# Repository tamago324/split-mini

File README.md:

# split mini

小さな分割キーボードです。

## ライセンス

<br />この 作品 は <a rel="license" href="http://creativecommons.org/licenses/by/4.0/">クリエイティブ・コモンズ 表示 4.0 国際 ライセンス</a>の下に提供されています。

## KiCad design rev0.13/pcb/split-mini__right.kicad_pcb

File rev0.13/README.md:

## split mini rev0.13

* [KLE](http://www.keyboard-layout-editor.com/#/gists/a34cca681a2130594f6d9f4207fc3f27)
* https://kbplate.ai03.com/ でプレートデータを作成
  * width: 17
  * height: 17
* 左右分割キーボード
* 狭ピッチ
  * キーキャップは専用のものを使う (底面が16mmのやつを使うことにする)
  * [雰囲気で作ったキーキャップ](https://github.com/tamago324/small-keycaps)
* MXのみ 対応
* 100mmx100mm以下のため、Elecrow で1ドルで発注可能
* [QMK firmware](https://github.com/tamago324/qmk_firmware/tree/tamago324/keyboards/tamago324/splitmini)
  * rev13 のディレクトリのため、`nix-shell --run 'sudo make tamago324/splitmini/rev13:tamago324:flash'` のようにして書き込み可能

## 部品一覧

片手分

| 名前                      | 値    | 備考                | 個数 | 部品番号   | リンク        |
| ---                       | ---   | ---                 | ---  | ---        | ---           |
| コンデンサ                | 0.1uF | 0805 (2012)         | 3    | C2、C3、C4 | [Digikey][1]  |
| コンデンサ                | 10uF  | 0805 (2012)         | 1    | C5         | [Digikey][2]  |
| コンデンサ                | 1uF   | 0805 (2012)         | 1    | C1         | [Digikey][3]  |
| コンデンサ                | 22pF  | 0805 (2012)         | 2    | C6、C7     | [Digikey][4]  |
| ヒューズ                  | 500mA | 1206 (3216)         | 1    | F1         | [Digikey][5]  |
| 抵抗                      | 5.1kΩ  | 0805 (2012)         | 2    | R1、R2     | [モノタロウ][13]  |
| 抵抗                      | 22    | 0805 (2012)         | 2    | R3、R4     | [Digikey][7]  |
| 抵抗                      | 10kΩ  | 0805 (2012)         | 2    | R5、R6     | [Digikey][6]  |
| 水晶発振子                | 16MHz | 3225 4pin 3.2x2.5mm | 1    | Y1         | [Digikey][8]  |
| TRRSジャック (MJ-4PP-9)   | -     | -                   | 1    | J2         | [遊舎工房][9] |
| ATmega32U4                | -     | 10x10mm P0.8mm      | 1    | U1         | [Digikey][10] |
| USBコネクタ (Type-C) | -     | 5077CR-16SMC2-BK-TR    | 1    | J1       | [秋月電子][11] |
| リセットスイッチ          | -     | SKRPACE010            | 1    | RESET1        | [秋月電子][12] |

### 実際に購入したところ

| 名前                      | 値    | 備考                | 個数 | 部品番号   | リンク        |
| ---                       | ---   | ---                 | ---  | ---        | ---           |
| コンデンサ                | 0.1uF | 0805 (2012)         | 3    | C2、C3、C4 | [秋月電子][21]  |
| コンデンサ                | 10uF  | 0805 (2012)         | 1    | C5         | [秋月電子][22]  |
| コンデンサ                | 1uF   | 0805 (2012)         | 1    | C1         | [秋月電子][23]  |
| コンデンサ                | 22pF  | 0805 (2012)         | 2    | C6、C7     | [mouser][24]  |
| ヒューズ                  | 500mA | 1206 (3216)         | 1    | F1         | [mouser][25]  |
| 抵抗                      | 5.1kΩ  | 0805 (2012)         | 2    | R1、R2     | [モノタロウ][13]  |
| 抵抗                      | 22    | 0805 (2012)         | 2    | R3、R4     | [mouser][27]  |
| 抵抗                      | 10kΩ  | 0805 (2012)         | 2    | R5、R6     | [秋月電子][26]  |
| 水晶発振子                | 16MHz | 3225 4pin 3.2x2.5mm | 1    | Y1         | [秋月電子][28]  |
| TRRSジャック (MJ-4PP-9)   | -     | -                   | 1    | J1         | [遊舎工房][29] |
| ATmega32U4                | -     | 10x10mm P0.8mm      | 1    | U1         | [秋月電子][30] |
| USBコネクタ (Type-C) | -     | 5077CR-16SMC2-BK-TR    | 1    | J1       | [秋月電子][11] |
| リセットスイッチ          | -     | SKRPACE010           | 1    | SW1        | [秋月電子][12] |

### 画像

#### PCB

#### ケース

## 参考情報

* https://github.com/ruiqimao/keyboard-pcb-guide
* [ATmega32u2直付けのキーパッドを作ろう！](https://taro-hayashi.github.io/LetsMakeaKeypadWithAtmega32u2/)
* [ATMega32u4を使う場合の設計メモ\.md](https://gist.github.com/s-show/286ffb1f5d9c886b514ff7a37e6d8d37)
* [ATmega32U4について学んだこと](https://zenn.dev/koron/articles/a2e220d73800ba)
* [Using USB Type\-C on hobyist projects – The blog of Tyler Ward \(aka scorpia\)](https://www.scorpia.co.uk/2016/03/17/using-usb-type-c-on-hobyist-projects/)

[1]:https://www.digikey.com/product-detail/en/samsung-electro-mechanics/CL21B104MBCNNNC/1276-2450-1-ND/3890536
[2]:https://www.digikey.com/product-detail/en/samsung-electro-mechanics/CL21A106KOQNNNG/1276-6455-1-ND/5958083
[3]:https://www.digikey.com/product-detail/en/samsung-electro-mechanics/CL21B105KAFNNNE/1276-1066-1-ND/3889152
[4]:https://www.digikey.com/product-detail/en/samsung-electro-mechanics/CL21C220JB61PNC/1276-2605-1-ND/3890691
[5]:https://www.digikey.com/product-detail/en/bel-fuse-inc/0ZCJ0050AF2E/507-1803-1-ND/4156312
[6]:https://www.digikey.com/product-detail/en/panasonic-electronic-components/ERA-6AEB103V/P10KDACT-ND/1465971
[7]:https://www.digikey.com/product-detail/en/panasonic-electronic-components/ERJ-6GEYJ220V/P22ACT-ND/87316
[8]:https://www.digikey.com/product-detail/en/CX3225SB16000D0GZJC1/1253-1698-1-ND/5995245/?itemSeq=264931473
[9]:https://shop.yushakobo.jp/products/a0800tr-01-1
[10]:https://www.digikey.com/product-detail/en/microchip-technology/ATMEGA32U4-AU/ATMEGA32U4-AU-ND/1914602
[11]:https://akizukidenshi.com/catalog/g/gC-14356/
[12]:https://akizukidenshi.com/catalog/g/gP-06185/
[13]:https://www.monotaro.com/g/04269677/?t.q=5.1K%20%E3%83%81%E3%83%83%E3%83%97%E6%8A%B5%E6%8A%97

[21]:https://akizukidenshi.com/catalog/g/gP-00093/
[22]:https://akizukidenshi.com/catalog/g/gP-13606/
[23]:https://akizukidenshi.com/catalog/g/gP-15331/
[24]:https://www.mouser.jp/ProductDetail/Samsung-Electro-Mechanics/CL21C220JB61PNC?qs=uvHW8qpSFORHMf5PV5yOeg%3D%3D
[25]:https://www.mouser.jp/ProductDetail/Bel-Fuse/0ZCJ0050AF2E?qs=SRYZG9HaIQ3Oqm1PQp276Q%3D%3D
[26]:https://akizukidenshi.com/catalog/g/gR-11797/
[27]:https://www.mouser.jp/ProductDetail/Panasonic/ERJ-6GEYJ220V?qs=tQNqqtTOejK5J3XsPrLscg%3D%3D
[28]:https://akizukidenshi.com/catalog/g/gP-02457/
[29]:https://shop.yushakobo.jp/products/a0800tr-01-1
[30]:https://akizukidenshi.com/catalog/g/gI-09835/

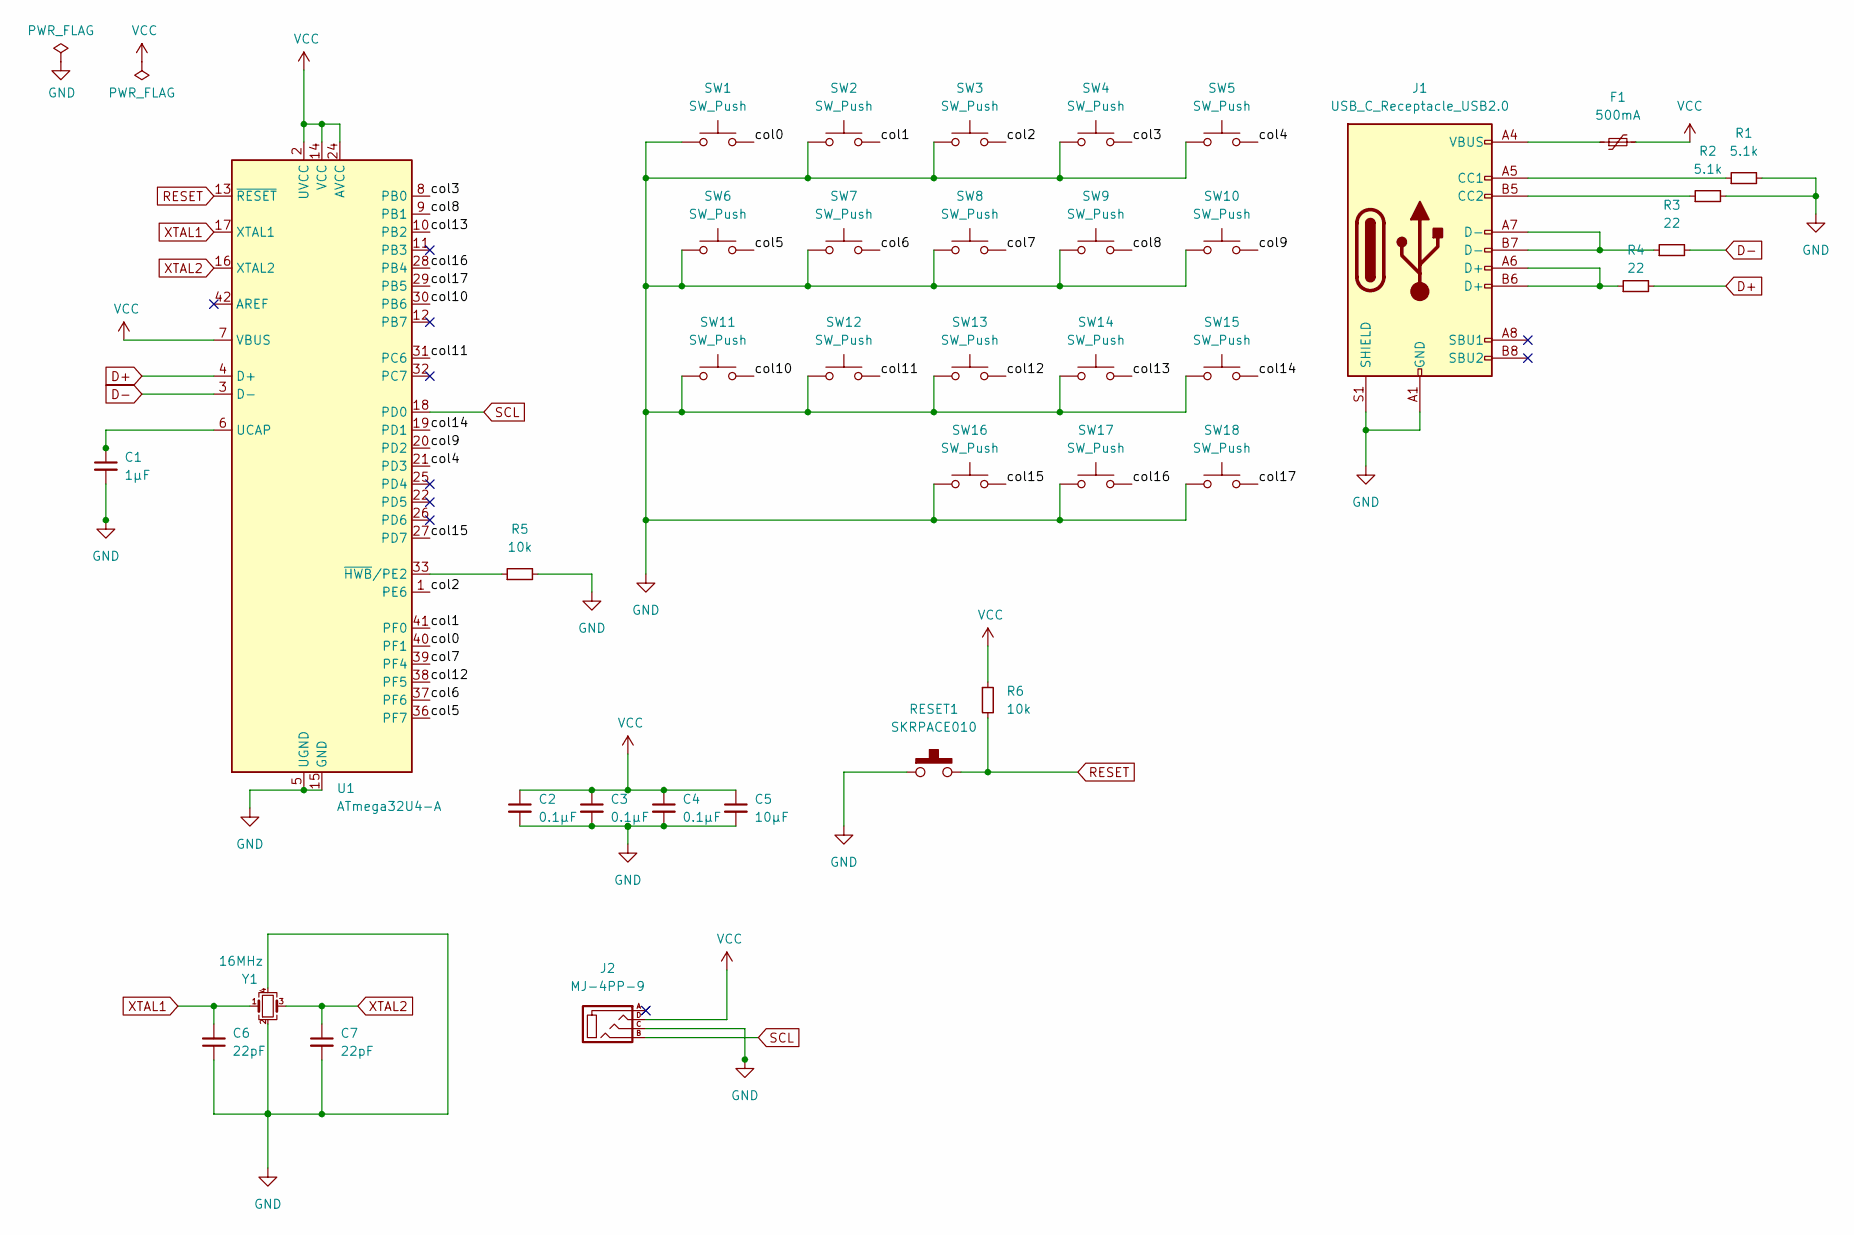
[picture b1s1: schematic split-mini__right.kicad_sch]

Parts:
C1: 1μF; C_0805_2012Metric; LCSC C28323
C2, C3, C4: 0.1μF; C_0805_2012Metric; LCSC C49678
C5: 10μF; C_0805_2012Metric; LCSC C440198
C6, C7: 22pF; C_0805_2012Metric; LCSC C1804
F1: 500mA; Fuse_1206_3216Metric; LCSC C883125
J1: USB_C_Receptacle_USB2.0; USB_C_Receptacle_Neltron_5077CR-16SMC2
J2: MJ-4PP-9; MJ-4PP-9_1side
R1, R2: 5.1k; R_0805_2012Metric; LCSC C17561
R3, R4: 22; R_0805_2012Metric; LCSC C17561
R5, R6: 10k; R_0805_2012Metric; LCSC C17414
RESET1: SKRPACE010; SKRPAxE010
SW1, SW2, SW3, SW4, SW5, SW6, SW7, SW8, SW9, SW10, SW11, SW12, SW13, SW14, SW15, SW16, SW17, SW18: SW_Push; CherryMX_Hotswap
U1: ATmega32U4-A; LQFP-44_10x10mm_P0.8mm
Y1: 16MHz; Crystal_SMD_SeikoEpson_FA238-4Pin_3.2x2.5mm_HandSoldering; LCSC C13738

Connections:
/col0: SW1.2, U1.40 (PF1)
/col1: SW2.2, U1.41 (PF0)
/col2: SW3.2, U1.1 (PE6)
/col3: SW4.2, U1.8 (PB0)
/col4: SW5.2, U1.21 (PD3)
/col5: SW6.2, U1.36 (PF7)
/col6: SW7.2, U1.37 (PF6)
/col7: SW8.2, U1.39 (PF4)
/col8: SW9.2, U1.9 (PB1)
/col9: SW10.2, U1.20 (PD2)
/col10: SW11.2, U1.30 (PB6)
/col11: SW12.2, U1.31 (PC6)
/col12: SW13.2, U1.38 (PF5)
/col13: SW14.2, U1.10 (PB2)
/col14: SW15.2, U1.19 (PD1)
/col15: SW16.2, U1.27 (PD7)
/col16: SW17.2, U1.28 (PB4)
/col17: SW18.2, U1.29 (PB5)
D+: R4.2, U1.4 (D+)
D-: R3.2, U1.3 (D-)
GND: C1.2, C2.2, C3.2, C4.2, C5.2, C6.1, C7.2, J1.A1 (GND), J1.A12 (GND), J1.B1 (GND), J1.B12 (GND), J1.S1 (SHIELD), J2.C, R1.2, R2.2, R5.2, RESET1.1 (A), RESET1.2 (B), SW1.1, SW2.1, SW3.1, SW4.1, SW5.1, SW6.1, SW7.1, SW8.1, SW9.1, SW10.1, SW11.1, SW12.1, SW13.1, SW14.1, SW15.1, SW16.1, SW17.1, SW18.1, U1.5 (UGND), U1.15 (GND), U1.23 (GND), U1.35 (GND), U1.43 (GND), Y1.2, Y1.4
unnamed: C1.1, U1.6 (UCAP)
unnamed: F1.1, J1.A4 (VBUS), J1.A9 (VBUS), J1.B4 (VBUS), J1.B9 (VBUS)
unnamed: J1.A5 (CC1), R1.1
unnamed: J1.A6 (D+), J1.B6 (D+), R4.1
unnamed: J1.A7 (D-), J1.B7 (D-), R3.1
unnamed: J1.B5 (CC2), R2.1
unnamed: R5.1, U1.33 (~HWB/PE2)
RESET: R6.2, RESET1.3 (C), RESET1.4 (D), U1.13 (~RESET)
SCL: J2.B, U1.18 (PD0)
VCC: C2.1, C3.1, C4.1, C5.1, F1.2, J2.D, R6.1, U1.2 (UVCC), U1.7 (VBUS), U1.14 (VCC), U1.24 (AVCC), U1.34 (VCC), U1.44 (AVCC)
XTAL1: C6.2, U1.17 (XTAL1), Y1.1
XTAL2: C7.1, U1.16 (XTAL2), Y1.3

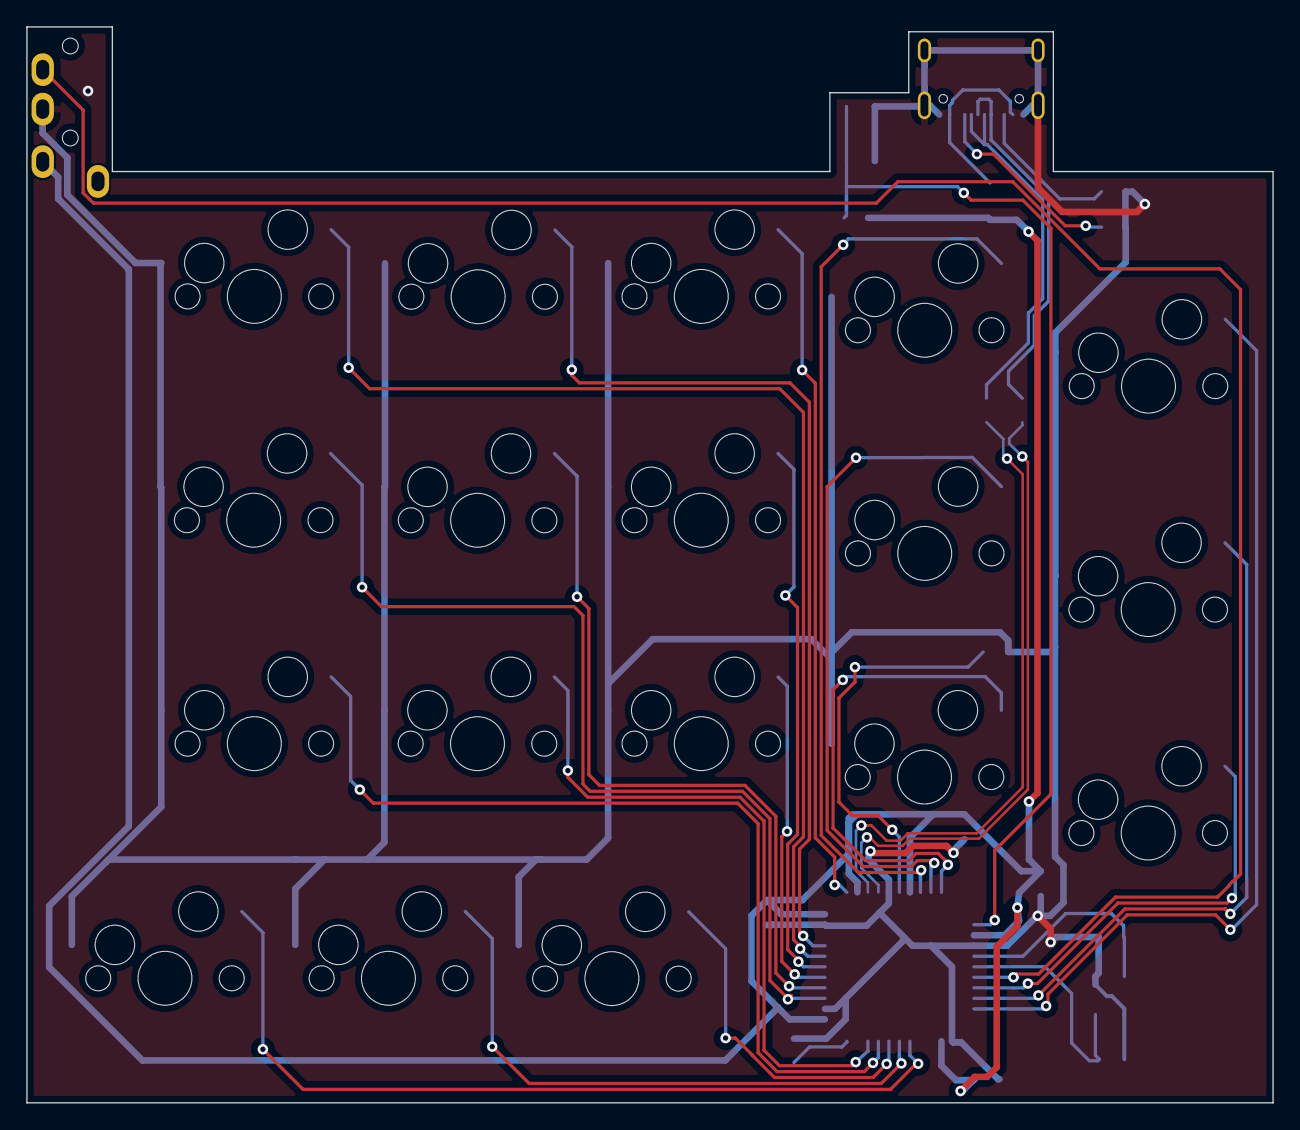
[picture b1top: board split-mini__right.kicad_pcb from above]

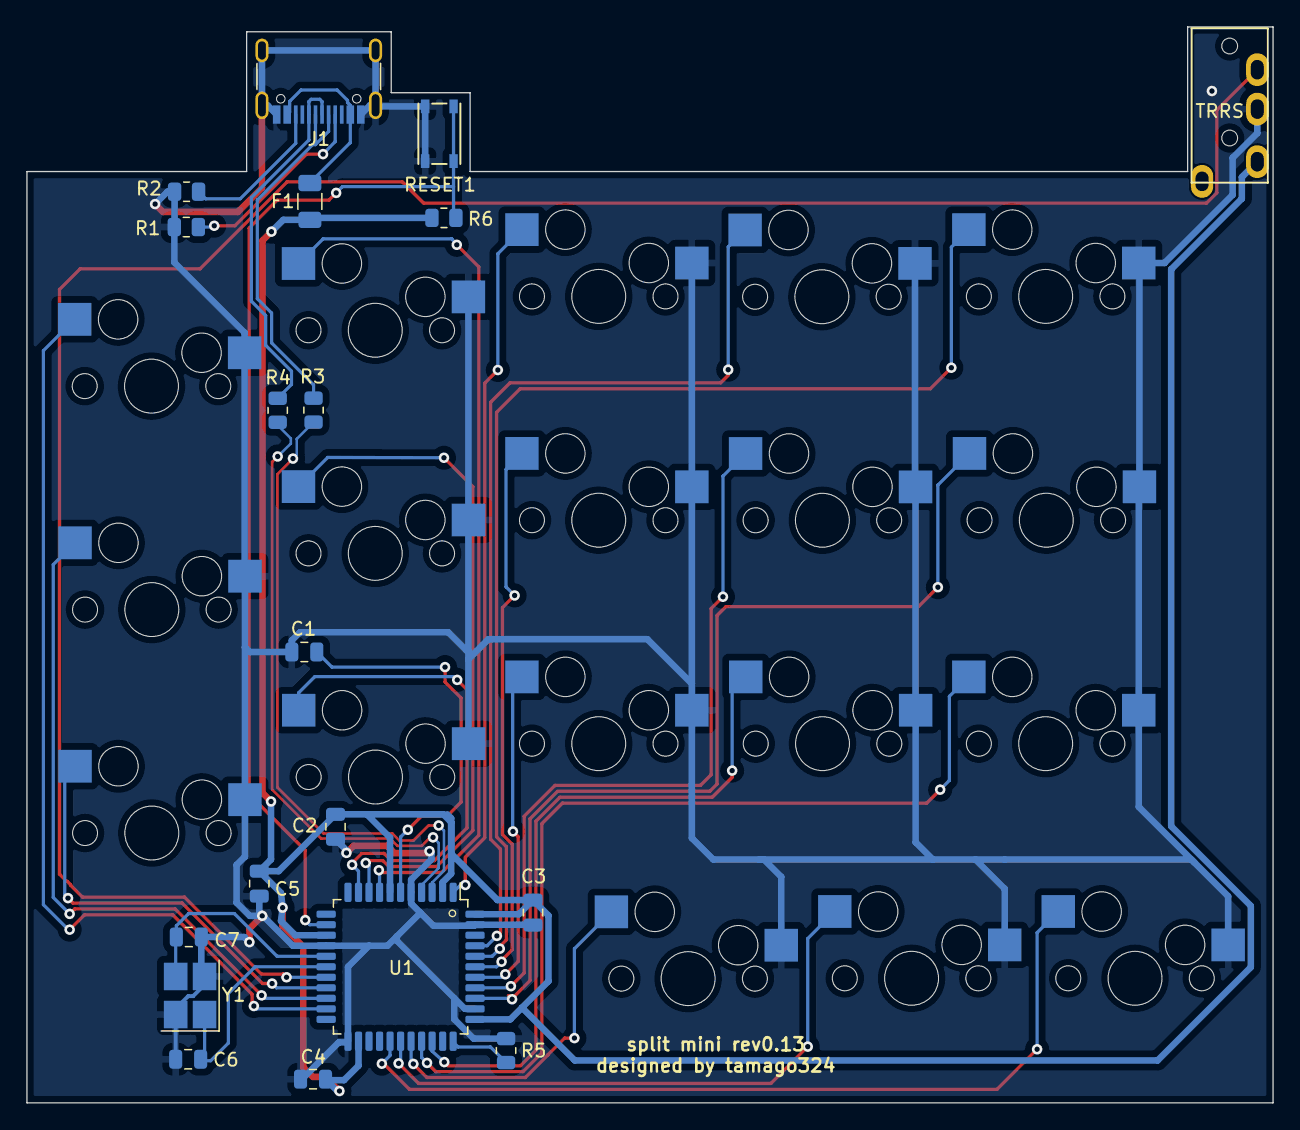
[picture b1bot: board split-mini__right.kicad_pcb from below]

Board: 2 copper layers, 94.8 x 81.8 mm, 37 parts (19 on the bottom side), 33 nets.

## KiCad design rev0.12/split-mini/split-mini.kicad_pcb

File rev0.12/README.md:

## split mini rev0.12

* ProMicro を使用
* [KLE](http://www.keyboard-layout-editor.com/##@_name=split%20mini%20rev0.13&notes=oyayubi%20ga%201.25%20ninatteiruyatu%0Amata,%20tatewo%2017.5%20ni%20sitai%3B&@_y:0.75&x:3&a:7%3B&=&=%3B&@_y:-0.9&x:5%3B&=%3B&@_y:-0.9500000000000001&x:2%3B&=%3B&@_y:-0.7&x:1%3B&=%3B&@_y:-0.44999999999999996&x:3%3B&=&=%3B&@_y:-0.8999999999999999&x:5%3B&=%3B&@_y:-0.9500000000000002&x:2%3B&=%3B&@_y:-0.6999999999999997&x:1%3B&=%3B&@_y:-0.4500000000000002&x:3%3B&=&=%3B&@_y:-0.8999999999999999&x:5%3B&=%3B&@_y:-0.9500000000000002&x:2%3B&=%3B&@_y:-0.6999999999999997&x:1%3B&=%3B&@_y:-0.3500000000000001&x:3.3%3B&=&_w:1.25%3B&=%3B&@_r:10&y:-2.05&x:6.3&w:1.25%3B&=)
* https://kbplate.ai03.com/ でプレートデータを作成
  * width: 16.5
  * height: 17.5
* 左右分割キーボード
* 狭ピッチ
  * キーキャップは専用のものを使う (底面が16mmのやつを使うことにする)
* MX 対応
* 100mmx100mm以下のため、Elecrow で1ドルで発注可能
  * PCB、トッププレート1つ、ボトムプレートの3つを3ドルで発注できて、2セット組み立てられる
* Trackball module をつけられる
  * 線をはんだ付けすることで使用可能になる想定
  * Aliexpress で売っているもの
    * [ケーブル](https://ja.aliexpress.com/item/4000898605030.html?spm=a2g0o.order_list.order_list_main.5.2968585aQbozum&gatewayAdapt=glo2jpn)
    * [コネクタ](https://ja.aliexpress.com/item/4001115739803.html?spm=a2g0o.order_list.order_list_main.11.2968585aQbozum&gatewayAdapt=glo2jpn)

## Pictures

### PCB

### Top plate

### bottom plate

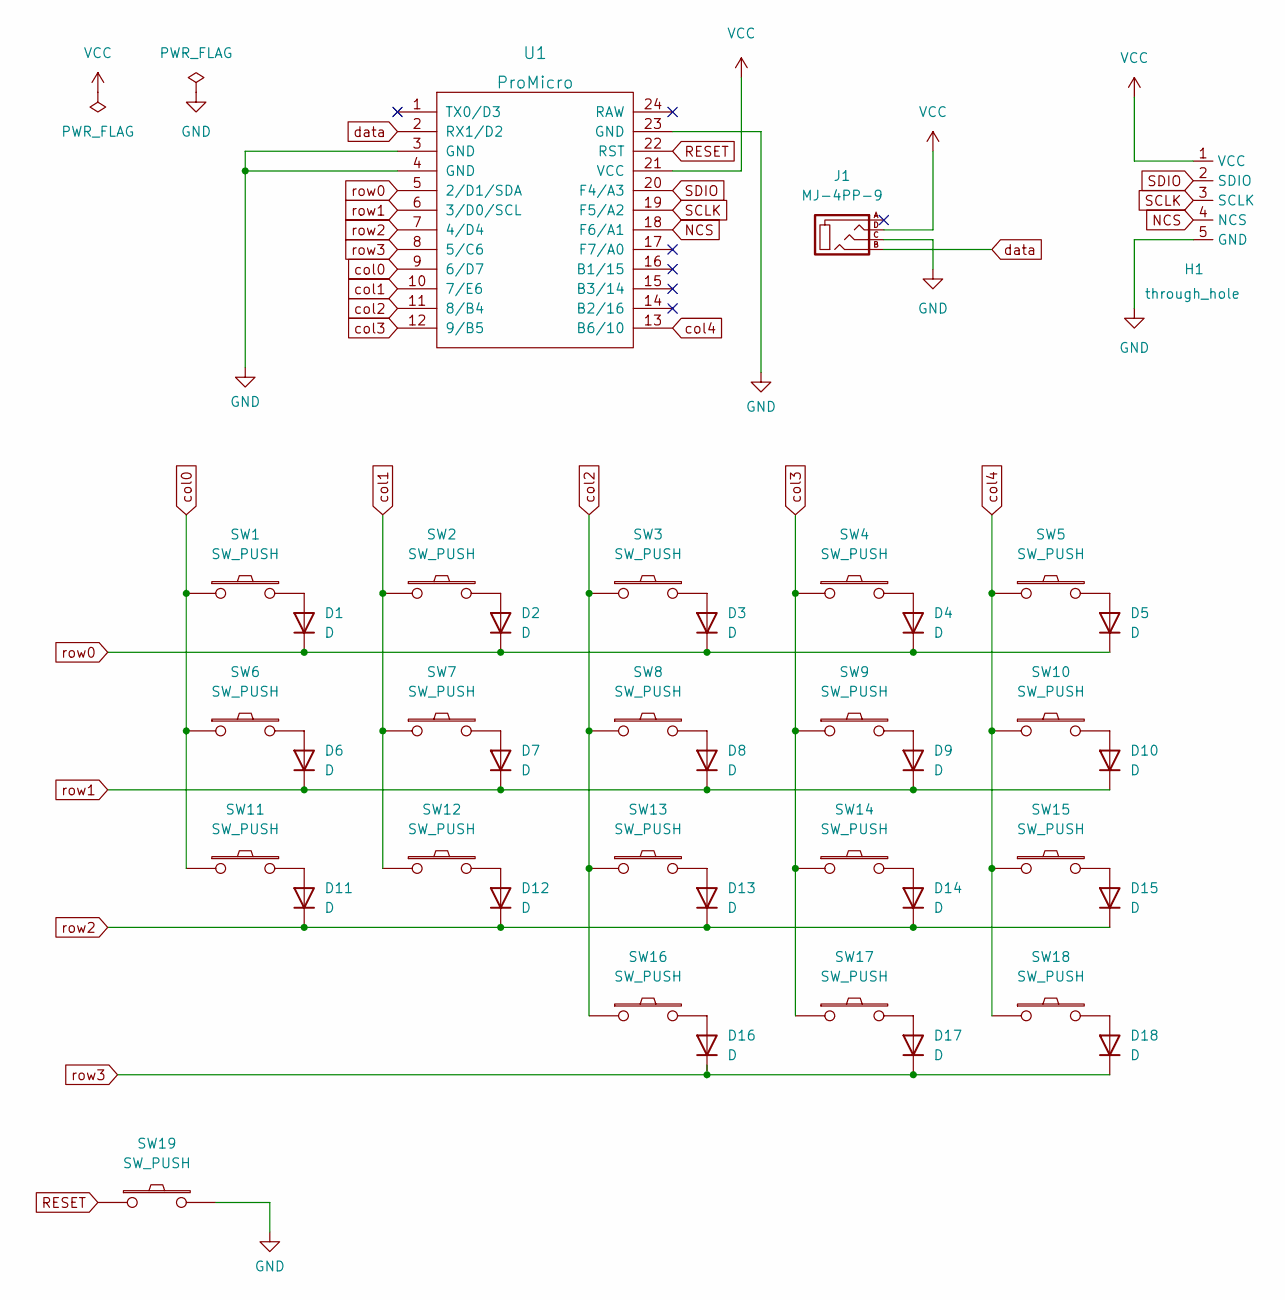
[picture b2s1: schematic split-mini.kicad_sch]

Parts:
D1, D2, D3, D4, D5, D6, D7, D8, D9, D10, D11, D12, D13, D14, D15, D16, D17, D18: D; D3_SMD
H1: through_hole; through hole 5pin
J1: MJ-4PP-9
SW1, SW2, SW3, SW4, SW5, SW6, SW7, SW8, SW9, SW10, SW11, SW12, SW13, SW14, SW15, SW16, SW17, SW18: SW_PUSH; MX-Hotswap-1U
SW19: SW_PUSH; ResetSW
U1: ProMicro; ProMicro_v2

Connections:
GND: H1.5 (GND), J1.C, SW19.2, U1.3 (GND), U1.4 (GND), U1.23 (GND)
NCS: H1.4 (NCS), U1.18 (F6/A1)
unnamed: D1.2 (A), SW1.2
unnamed: D2.2 (A), SW2.2
unnamed: D3.2 (A), SW3.2
unnamed: D4.2 (A), SW4.2
unnamed: D5.2 (A), SW5.2
unnamed: D6.2 (A), SW6.2
unnamed: D7.2 (A), SW7.2
unnamed: D8.2 (A), SW8.2
unnamed: D9.2 (A), SW9.2
unnamed: D10.2 (A), SW10.2
unnamed: D11.2 (A), SW11.2
unnamed: D12.2 (A), SW12.2
unnamed: D13.2 (A), SW13.2
unnamed: D14.2 (A), SW14.2
unnamed: D15.2 (A), SW15.2
unnamed: D16.2 (A), SW16.2
unnamed: D17.2 (A), SW17.2
unnamed: D18.2 (A), SW18.2
RESET: SW19.1, U1.22 (RST)
SCLK: H1.3 (SCLK), U1.19 (F5/A2)
SDIO: H1.2 (SDIO), U1.20 (F4/A3)
VCC: H1.1 (VCC), J1.D, U1.21 (VCC)
col0: SW1.1, SW6.1, SW11.1, U1.9 (6/D7)
col1: SW2.1, SW7.1, SW12.1, U1.10 (7/E6)
col2: SW3.1, SW8.1, SW13.1, SW16.1, U1.11 (8/B4)
col3: SW4.1, SW9.1, SW14.1, SW17.1, U1.12 (9/B5)
col4: SW5.1, SW10.1, SW15.1, SW18.1, U1.13 (B6/10)
data: J1.B, U1.2 (RX1/D2)
row0: D1.1 (K), D2.1 (K), D3.1 (K), D4.1 (K), D5.1 (K), U1.5 (2/D1/SDA)
row1: D6.1 (K), D7.1 (K), D8.1 (K), D9.1 (K), D10.1 (K), U1.6 (3/D0/SCL)
row2: D11.1 (K), D12.1 (K), D13.1 (K), D14.1 (K), D15.1 (K), U1.7 (4/D4)
row3: D16.1 (K), D17.1 (K), D18.1 (K), U1.8 (5/C6)

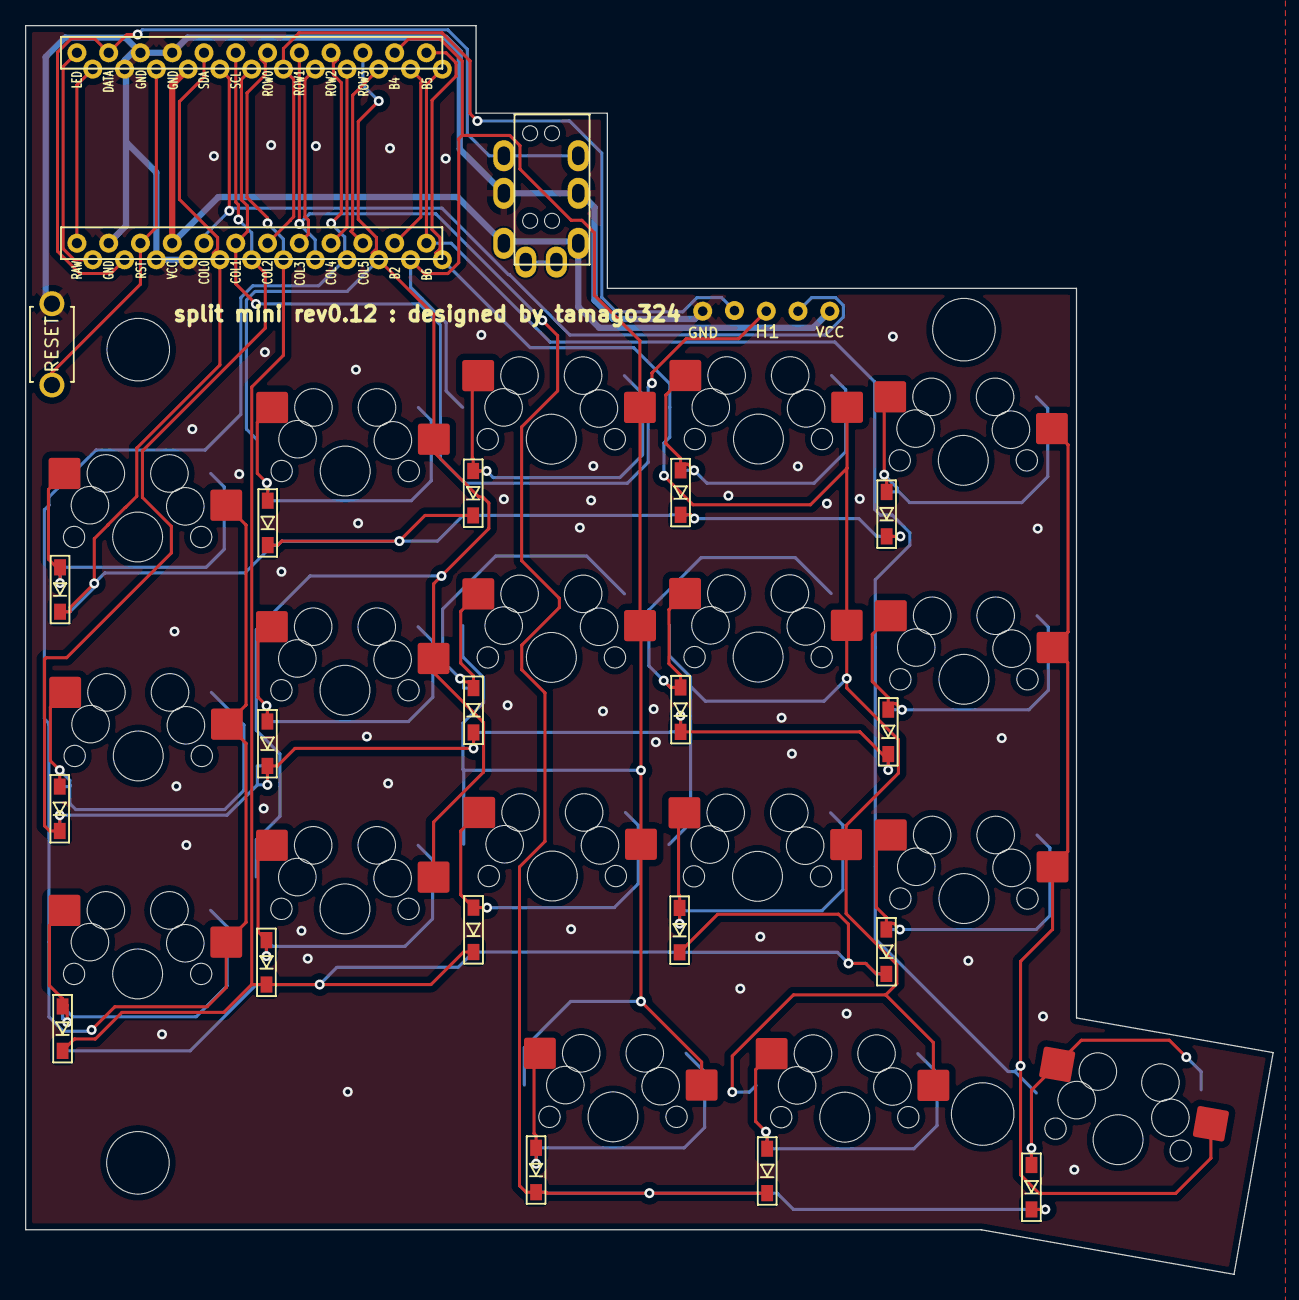
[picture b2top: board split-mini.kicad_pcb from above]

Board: 2 copper layers, 99.7 x 99.8 mm, 44 parts (0 on the bottom side), 34 nets.

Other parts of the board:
HOLE1, HOLE2, HOLE3: Val**; M2_HOLE_v2_4.5mm
HOLE4: Val*; M2_HOLE_v2_4.5mm

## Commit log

2022-09-17 init
2022-09-17 add README
2022-09-19 rev0.1 のREADME.md を修正
2022-09-19 rev0.1 の READMD を修正
2022-09-19 rev0.2 の README を修正
2022-10-07 add rev0.3
2022-10-07 画像追加
2022-10-07 add QMK firmware link
2022-11-03 rev0.4 を追加
2022-11-03 kle の URL を追加
2022-11-22 rev0.5 を追加
2022-11-22 rev0.4 を削除
2022-11-23 rev0.5 の REWADME を更新
2022-11-30 いろいろ追加
2022-11-30 update 写真を追加
2022-11-30 fix case link
2022-12-13 add rev0.9
2023-01-03 rev.0.12 を追加
2023-01-03 rename
2023-02-03 add rev0.13
2023-02-06 prk_firmware 削除

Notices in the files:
README.md:
CC BY 4.0
